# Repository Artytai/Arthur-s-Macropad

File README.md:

# Arthur's Macropad
Firmware:

This hackpad uses KMK firmware, a Python-based keyboard firmware that runs on CircuitPython and is well suited for small custom macropads.

The firmware is written for a Seeed XIAO RP2040 and uses direct GPIO scanning (no key matrix). Each of the five switches is connected to an individual GPIO pin and pulled to ground when pressed. The firmware scans these pins using KMK’s KeysScanner.

The project also includes support for two SK6812 MINI RGB LEDs, chained together and driven from a single data pin on the XIAO.

The firmware source can be found in the Firmware/ folder as main.py.
At submission time, the firmware has not been flashed to hardware, but it is logically complete and matches the PCB schematic and pinout.

Firmware stack:

Firmware: KMK

Language: Python

Runtime: CircuitPython

BILL OF MATERIALS:
| Item              | Quantity | Part                                    | Notes                |
| ----------------- | -------- | --------------------------------------- | -------------------- |
| Microcontroller   | 1        | Seeed Studio XIAO RP2040 (Through-Hole) | Main MCU             |
| Mechanical Switch | 5        | MX-style switches                       | Input keys           |
| Keycaps           | 5        | DSA keycaps                             | Fits MX switches     |
| Diodes            | 5        | 1N4148 (Through-Hole)                   | Switch isolation     |
| RGB LEDs          | 2        | SK6812 MINI-E                           | Addressable RGB LEDs |
| PCB               | 1        | Custom 2-layer PCB                      | ≤ 100mm × 100mm      |
| Case (Top)        | 1        | 3D printed                              | PLA / PETG           |
| Case (Bottom)     | 1        | 3D printed                              | PLA / PETG           |
| Screws            | 4        | M3 × 16mm                               | Case assembly        |
| Heat-set Inserts  | 4        | M3 × 5mm × 4mm                          | Case mounting        |
| USB Cable         | 1        | USB-C cable                             | Programming & power  |

Overall HackPad overview:
I modeled the 5-key design in Fusion 360. The top and bottom are held together using 4 M3x16 bolts

The MCU used in the CAD model was imported from PTC's Onshape. It was fitted to a green rectangular part symbolizing the PCB

Top cover:

Bottom with PCB and Bolts:

PCB Images:

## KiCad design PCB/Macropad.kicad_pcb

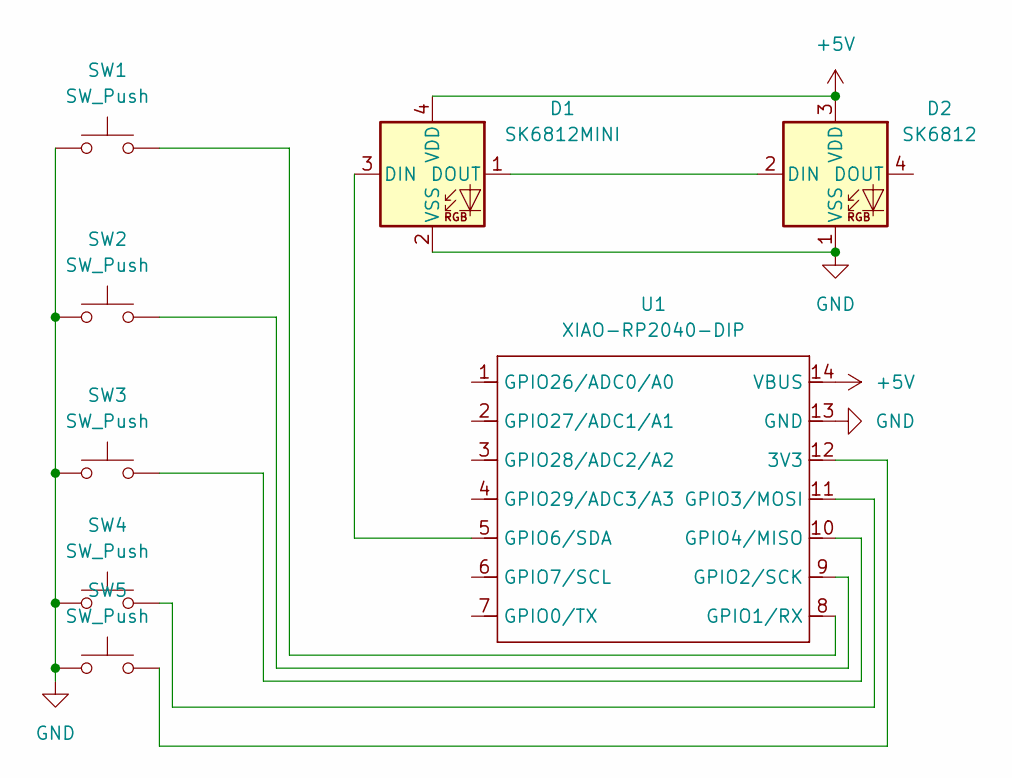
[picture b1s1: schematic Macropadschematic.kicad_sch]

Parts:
D1: SK6812MINI; LED_SK6812MINI_PLCC4_3.5x3.5mm_P1.75mm
D2: SK6812; LED_SK6812MINI_PLCC4_3.5x3.5mm_P1.75mm
SW1, SW2, SW3, SW4, SW5: SW_Push; SW_Cherry_MX_1.00u_PCB
U1: XIAO-RP2040-DIP

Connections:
+5V: D1.4 (VDD), D2.3 (VDD), U1.14 (VBUS)
GND: D1.2 (VSS), D2.1 (VSS), SW1.1, SW2.1, SW3.1, SW4.1, SW5.1, U1.13 (GND)
unnamed: D1.3 (DIN), U1.5 (GPIO6/SDA)
unnamed: D1.1 (DOUT), D2.2 (DIN)
unnamed: SW5.2, U1.12 (3V3)
unnamed: SW1.2, U1.8 (GPIO1/RX)
unnamed: SW2.2, U1.9 (GPIO2/SCK)
unnamed: SW4.2, U1.11 (GPIO3/MOSI)
unnamed: SW3.2, U1.10 (GPIO4/MISO)

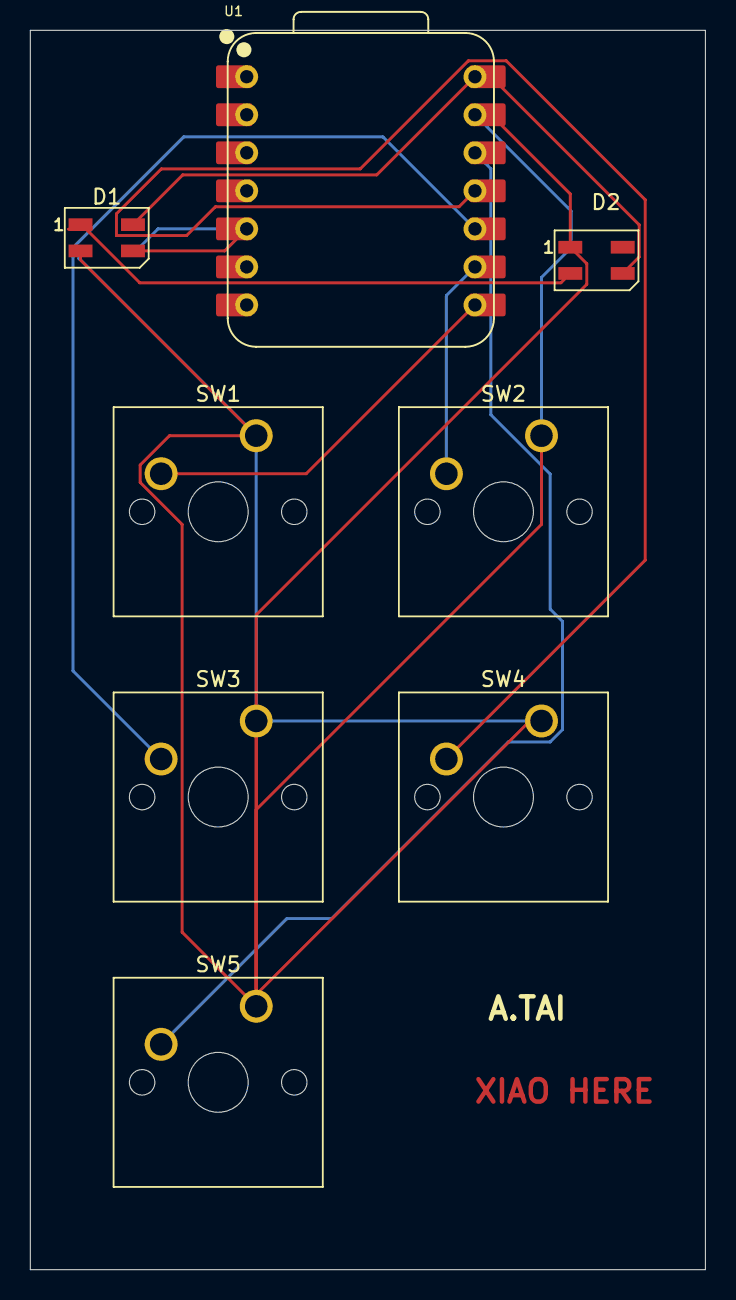
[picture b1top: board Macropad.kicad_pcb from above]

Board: 2 copper layers, 45.1 x 82.8 mm, 8 parts (0 on the bottom side), 9 nets.

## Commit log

2025-12-29 Add files via upload
    The Assembled Macropad-
    The MCU was imported, so the color is off-I had a hard time trying to import the original part, but to no avail.
2025-12-29 Add files via upload
    .kicadpro file
2025-12-29 Add files via upload
    Macropad PCB file
2025-12-29 Add files via upload
    Macropad PCB Schematic file
2025-12-29 Add files via upload
    My source code (it's KMK firmware).
    Language: Python
    Runs on: CircuitPython
